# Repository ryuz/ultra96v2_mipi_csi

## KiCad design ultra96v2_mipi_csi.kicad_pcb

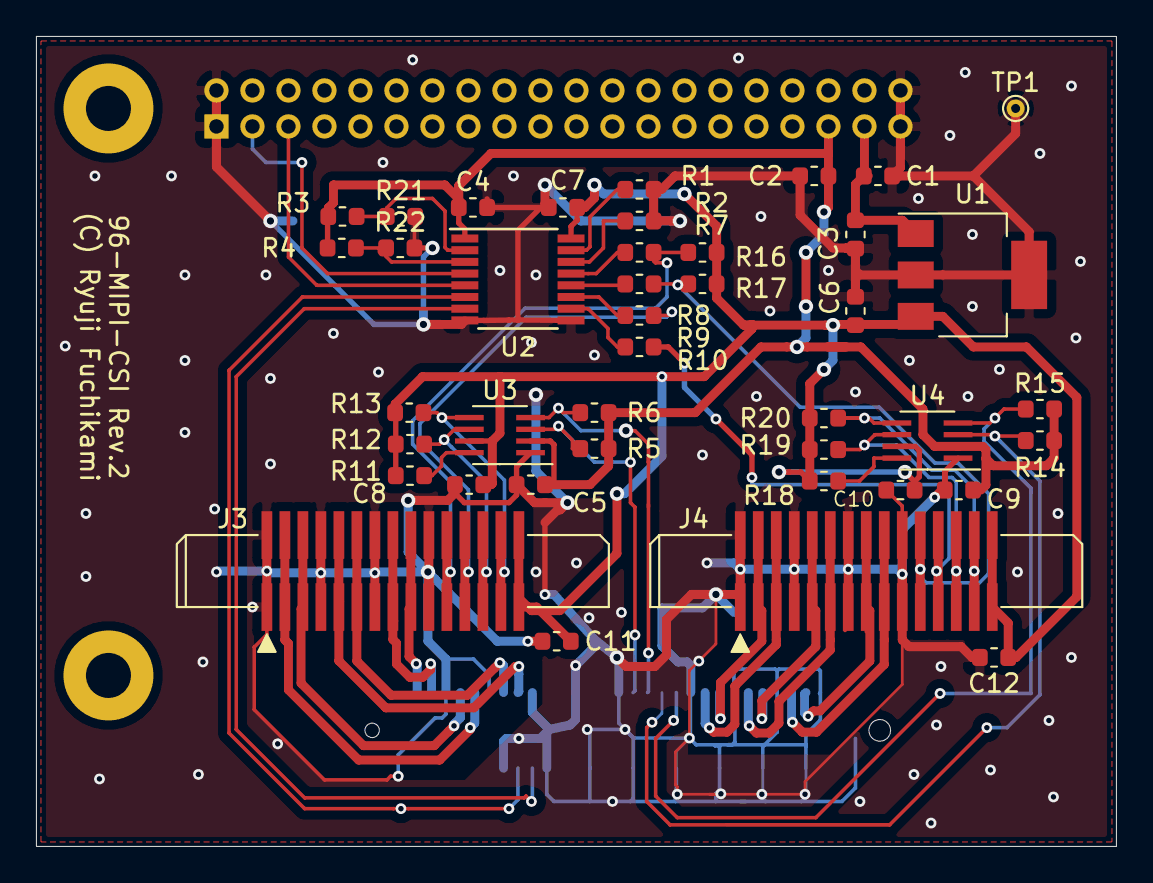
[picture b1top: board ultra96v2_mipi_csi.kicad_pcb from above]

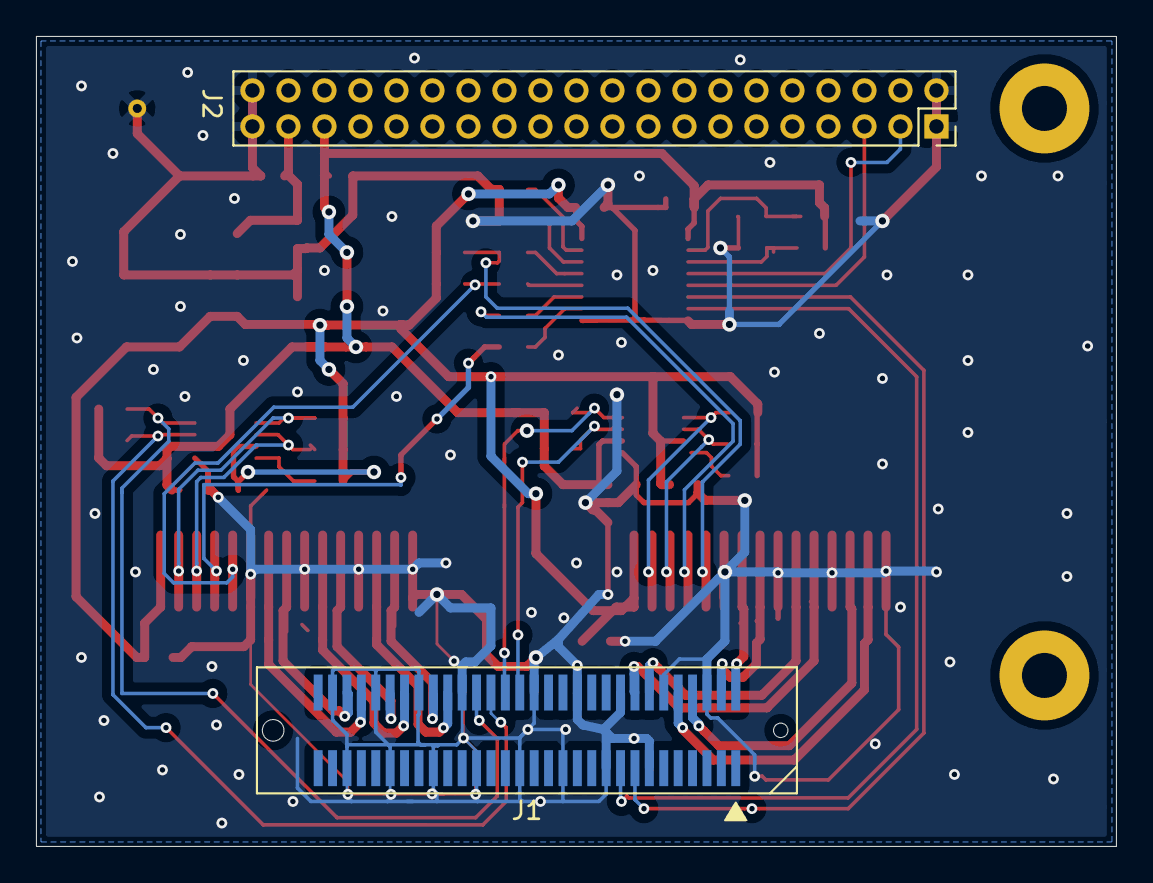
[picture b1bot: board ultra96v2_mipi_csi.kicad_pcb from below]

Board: 2 copper layers, 60.0 x 45.0 mm, 43 parts (2 on the bottom side), 42 nets.

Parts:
C1, C2: 10uF; C_0603_1608Metric
C3, C6: 4.7uF; C_0603_1608Metric
C4, C5, C7, C8, C9, C10, C11, C12: 0.1uF; C_0603_1608Metric
J1: 61083-063402LF
J2: 10075024-G01-20ULF; PinSocket_2x20_P2.00mm_Vertical
J3, J4: 1-1734248-5; 55510-140LF_handsolder
R1, R2, R3, R4, R7, R8, R9, R10, R11, R16, R17, R18: 0; R_0603_1608Metric
R5, R6, R12, R13, R14, R15, R19, R20: 4.7k; R_0603_1608Metric
R21, R22: <0>; R_0603_1608Metric
TP1: TestPoint; TestPoint_THTPad_D1.0mm_Drill0.5mm
U1: AP7361C-33E; SOT-223-3_TabPin2
U2: SN74AVC4T245PW; TSSOP-16_4.4x5mm_P0.65mm
U3, U4: PCA9306DCTR

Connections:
+1V8: C2.1, C4.1, C5.1, C9.1, J2.35, R3.2, R4.2, R5.2, R6.2, R14.2, R15.2, U2.1, U3.2, U4.2
+3V3: C6.1, C7.1, C8.1, C10.1, C11.1, C12.1, J3.15, J4.15, R11.1, R12.1, R13.1, R16.2, R17.2, R18.1, R19.1, R20.1, U1.3, U2.16, U3.7, U4.7
+5V: C1.1, C3.1, J2.37, U1.1
/CAM0_CLK: J3.12, R9.1
/CAM0_GPIO: J3.11, R7.1, R16.1
/CAM0_SCL: J3.13, R12.2, U3.6
/CAM0_SDA: J3.14, R13.2, U3.5
/CAM1_CLK: J4.12, R10.1
/CAM1_GPIO: J4.11, R8.1, R17.1
/CAM1_SCL: J4.13, R19.2, U4.6
/CAM1_SDA: J4.14, R20.2, U4.5
/HS_CSI0_CLK_N: J1.4, J3.8
/HS_CSI0_CLK_P: J1.2, J3.9
/HS_CSI0_D0_N: J1.10, J3.2
/HS_CSI0_D0_P: J1.8, J3.3
/HS_CSI0_D1_N: J1.16, J3.5
/HS_CSI0_D1_P: J1.14, J3.6
/HS_CSI0_MCLK: J1.15, U2.6
/HS_CSI1_CLK_N: J1.56, J4.8
/HS_CSI1_CLK_P: J1.54, J4.9
/HS_CSI1_D0_N: J1.44, J4.2
/HS_CSI1_D0_P: J1.42, J4.3
/HS_CSI1_D1_N: J1.50, J4.5
/HS_CSI1_D1_P: J1.48, J4.6
/HS_CSI1_MCLK: J1.17, U2.7
/HS_I2C2_SCL: J1.32, R5.1, U3.3
/HS_I2C2_SDA: J1.34, R6.1, U3.4
/HS_I2C3_SCL: J1.36, R14.1, U4.3
/HS_I2C3_SDA: J1.38, R15.1, U4.4
/LS_GPIO_0: J2.3, U2.4
/LS_GPIO_1: J2.5, U2.5
GND: C1.2, C2.2, C3.2, C4.2, C5.2, C6.2, C7.2, C8.2, C9.2, C10.2, C11.2, C12.2, J1.6, J1.12, J1.13, J1.18, J1.19, J1.24, J1.25, J1.30, J1.31, J1.37, J1.40, J1.43, J1.46, J1.49, J1.52, J1.55, J1.58, J2.1, J2.2, J2.39, J2.40, J3.1, J3.4, J3.7, J3.10, J4.1, J4.4, J4.7, J4.10, R1.2, R2.2, R21.2, R22.2, TP1.1, U1.2, U2.8, U2.9, U3.1, U4.1
unnamed: R1.1, U2.15
unnamed: R2.1, U2.14
unnamed: R7.2, U2.13
unnamed: R8.2, U2.12
unnamed: R9.2, U2.11
unnamed: R10.2, U2.10
unnamed: R11.2, U3.8
unnamed: R18.2, U4.8
unnamed: R3.1, R21.1, U2.2
unnamed: R4.1, R22.1, U2.3

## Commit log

2020-01-13 1st commit
2020-01-19 この内容で発注
2020-03-08 rev2
